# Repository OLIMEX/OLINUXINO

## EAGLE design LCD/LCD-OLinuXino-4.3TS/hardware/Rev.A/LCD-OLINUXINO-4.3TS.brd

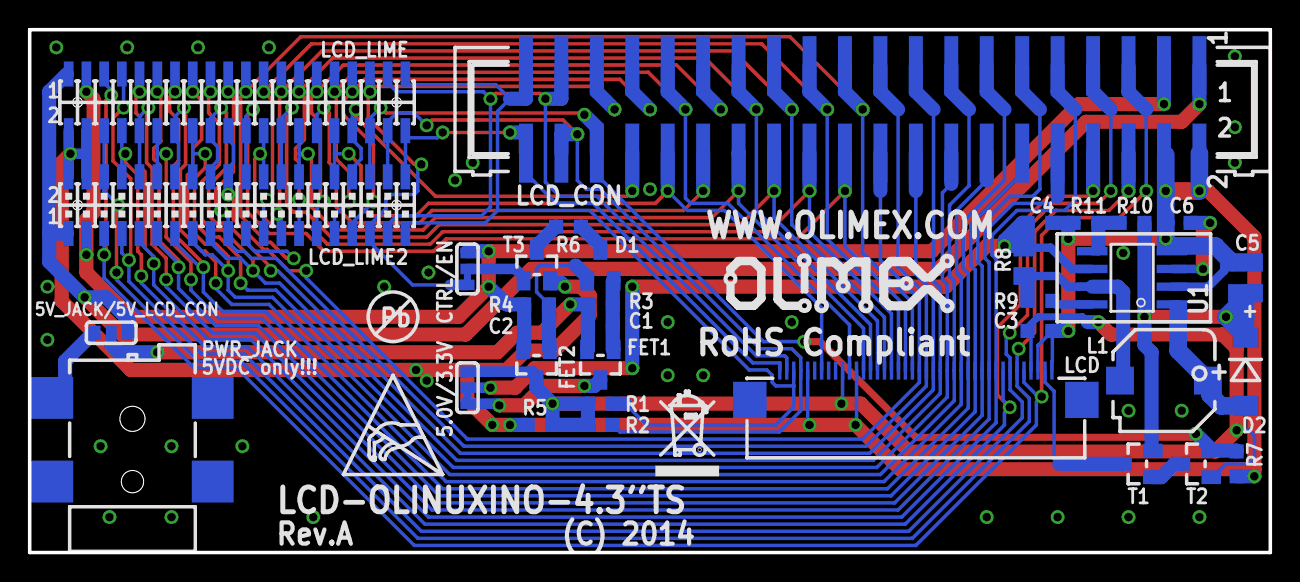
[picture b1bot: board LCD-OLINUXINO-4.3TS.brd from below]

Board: 2 copper layers, 88.9 x 37.5 mm, 38 parts (38 on the bottom side), 57 nets.

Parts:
5.0V/3.3V: 5.0V:Close/3.3V:Open; SJ_2_SMALL_23_TIED
5V_JACK/5V_LCD_CON: 5V_JACK:Open/5V_LCD_CON:Close; SJ_2_SMALL
C1, C3, C4: 22uF/6.3V; C0603_DWS
C2: 100n; C0603_DWS
C5: 100uF/35V/6.3x11; CP6.3X11-H-M
C6: 470pF; C0603_DWS
CTRL/EN: CTRL:Close/EN:Open; SJ_2_SMALL_23_TIED
D1: BAT54C; SOT23C
D2: 1N5819S(SS14); MLL-41
FET1, FET2: IRLML6402; SOT23
L1: 220uH/SD75; CLXXUH_SD73
LCD: BT043DC+(FPV-WZA21-40-LF); FPV-WZA21-40-LF
LCD_CON: ML40-GBH-254-SMT-40; ML40-MALE(GBH-254-SMT-40)
LCD_LIME: GPH127SMT-02X20; YA-V36P-2X20-LF
LCD_LIME2: GPH127SMT-02X20; GPH127SMT-02X20(PA-V16X-2X20-LF)
PWR_JACK: DCJ-W54R-20-LF; PWR-JACK-SMD
R1, R2: NA; R0603_5MIL_DWS
R3, R4, R10: 27k/1%; R0603_5MIL_DWS
R5: 10k; R0603_5MIL_DWS
R6: 1k; R0603_5MIL_DWS
R7, R11: 1.2k/1%; R0603_5MIL_DWS
R8: 1R; R0805_5MIL_DWS
R9: 150R; R0603_5MIL_DWS
T1: DTA114YKA; SOT-23
T2, T3: DTC114YKA; SOT-23
U1: MC34063AD(R2)G,(SO8); SO-8
U$4: PB_SMALL
U$8: OLIMEX1_V
U$10: ESD_SYMBOL
U$11: RECYCLE_BIN1/8

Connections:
3.3VDC: C2.1, CTRL/EN.1, FET2.2, LCD_CON.3, LCD_LIME.3, LCD_LIME2.3, R4.2
5VDC: 5V_JACK/5V_LCD_CON.2, C1.1, FET1.2, R3.2
+5V: 5.0V/3.3V.2, C4.1, R8.1, U1.6
+12V: C5.+, D2.K, R10.2, T1.2
GND: C3.2, C4.2, C5.-, C6.2, LCD.1, LCD.3, LCD.29, LCD.36, LCD_CON.2, LCD_CON.4, LCD_LIME.2, LCD_LIME.4, LCD_LIME2.2, LCD_LIME2.4, PWR_JACK.2, PWR_JACK.3, R5.1, R7.1, R11.1, T3.2, U1.2, U1.4
LCD_B0: LCD.21, LCD_CON.21, LCD_LIME.21, LCD_LIME2.21
LCD_B1: LCD.22, LCD_CON.22, LCD_LIME.22, LCD_LIME2.22
LCD_B2: LCD.23, LCD_CON.23, LCD_LIME.23, LCD_LIME2.23
LCD_B3: LCD.24, LCD_CON.24, LCD_LIME.24, LCD_LIME2.24
LCD_B4: LCD.25, LCD_CON.25, LCD_LIME.25, LCD_LIME2.25
LCD_B5: LCD.26, LCD_CON.26, LCD_LIME.26, LCD_LIME2.26
LCD_B6: LCD.27, LCD_CON.27, LCD_LIME.27, LCD_LIME2.27
LCD_B7: LCD.28, LCD_CON.28, LCD_LIME.28, LCD_LIME2.28
LCD_BKL: LCD_CON.36, LCD_LIME.36, LCD_LIME2.36, R7.2, T2.2
LCD_CLK: LCD.30, LCD_CON.31, LCD_LIME.31, LCD_LIME2.31
LCD_DE: LCD.34, LCD_CON.32, LCD_LIME.32, LCD_LIME2.32
LCD_G0: LCD.13, LCD_CON.13, LCD_LIME.13, LCD_LIME2.13
LCD_G1: LCD.14, LCD_CON.14, LCD_LIME.14, LCD_LIME2.14
LCD_G2: LCD.15, LCD_CON.15, LCD_LIME.15, LCD_LIME2.15
LCD_G3: LCD.16, LCD_CON.16, LCD_LIME.16, LCD_LIME2.16
LCD_G4: LCD.17, LCD_CON.17, LCD_LIME.17, LCD_LIME2.17
LCD_G5: LCD.18, LCD_CON.18, LCD_LIME.18, LCD_LIME2.18
LCD_G6: LCD.19, LCD_CON.19, LCD_LIME.19, LCD_LIME2.19
LCD_G7: LCD.20, LCD_CON.20, LCD_LIME.20, LCD_LIME2.20
LCD_PWRE: CTRL/EN.3, LCD_CON.35, LCD_LIME.35, LCD_LIME2.35
LCD_R0: LCD.5, LCD_CON.5, LCD_LIME.5, LCD_LIME2.5
LCD_R1: LCD.6, LCD_CON.6, LCD_LIME.6, LCD_LIME2.6
LCD_R2: LCD.7, LCD_CON.7, LCD_LIME.7, LCD_LIME2.7
LCD_R3: LCD.8, LCD_CON.8, LCD_LIME.8, LCD_LIME2.8
LCD_R4: LCD.9, LCD_CON.9, LCD_LIME.9, LCD_LIME2.9
LCD_R5: LCD.10, LCD_CON.10, LCD_LIME.10, LCD_LIME2.10
LCD_R6: LCD.11, LCD_CON.11, LCD_LIME.11, LCD_LIME2.11
LCD_R7: LCD.12, LCD_CON.12, LCD_LIME.12, LCD_LIME2.12
unnamed: 5.0V/3.3V.3, FET1.3
unnamed: T1.1, T2.3
unnamed: LCD_CON.29, LCD_LIME.29, LCD_LIME2.29
unnamed: LCD_CON.33, LCD_LIME.33, LCD_LIME2.33
unnamed: LCD_CON.30, LCD_LIME.30, LCD_LIME2.30
unnamed: LCD_CON.34, LCD_LIME.34, LCD_LIME2.34
unnamed: C2.2, D1.1, FET2.1, R4.1
unnamed: C1.2, D1.2, FET1.1, R3.1
unnamed: 5V_JACK/5V_LCD_CON.3, LCD_CON.1, LCD_LIME.1, LCD_LIME2.1
unnamed: R6.1, T3.3
unnamed: CTRL/EN.2, T3.1
unnamed: D1.3, R6.2
unnamed: 5V_JACK/5V_LCD_CON.1, PWR_JACK.1
unnamed: R10.1, R11.2, U1.5
unnamed: C6.1, U1.3
unnamed: D2.A, L1.2, U1.1
unnamed: L1.1, R8.2, R9.2, U1.7
unnamed: R9.1, U1.8
TPX1: LCD.37, LCD_CON.38, LCD_LIME.38, LCD_LIME2.38, R2.2
TPX2: LCD.39, LCD_CON.37, LCD_LIME.37, LCD_LIME2.37
TPY1: LCD.38, LCD_CON.39, LCD_LIME.39, LCD_LIME2.39, R1.2
TPY2: LCD.40, LCD_CON.40, LCD_LIME.40, LCD_LIME2.40
VCC: 5.0V/3.3V.1, C3.1, FET2.3, LCD.4, LCD.31, R1.1, R2.1, R5.2, T2.1
VLED+: LCD.2, T1.3

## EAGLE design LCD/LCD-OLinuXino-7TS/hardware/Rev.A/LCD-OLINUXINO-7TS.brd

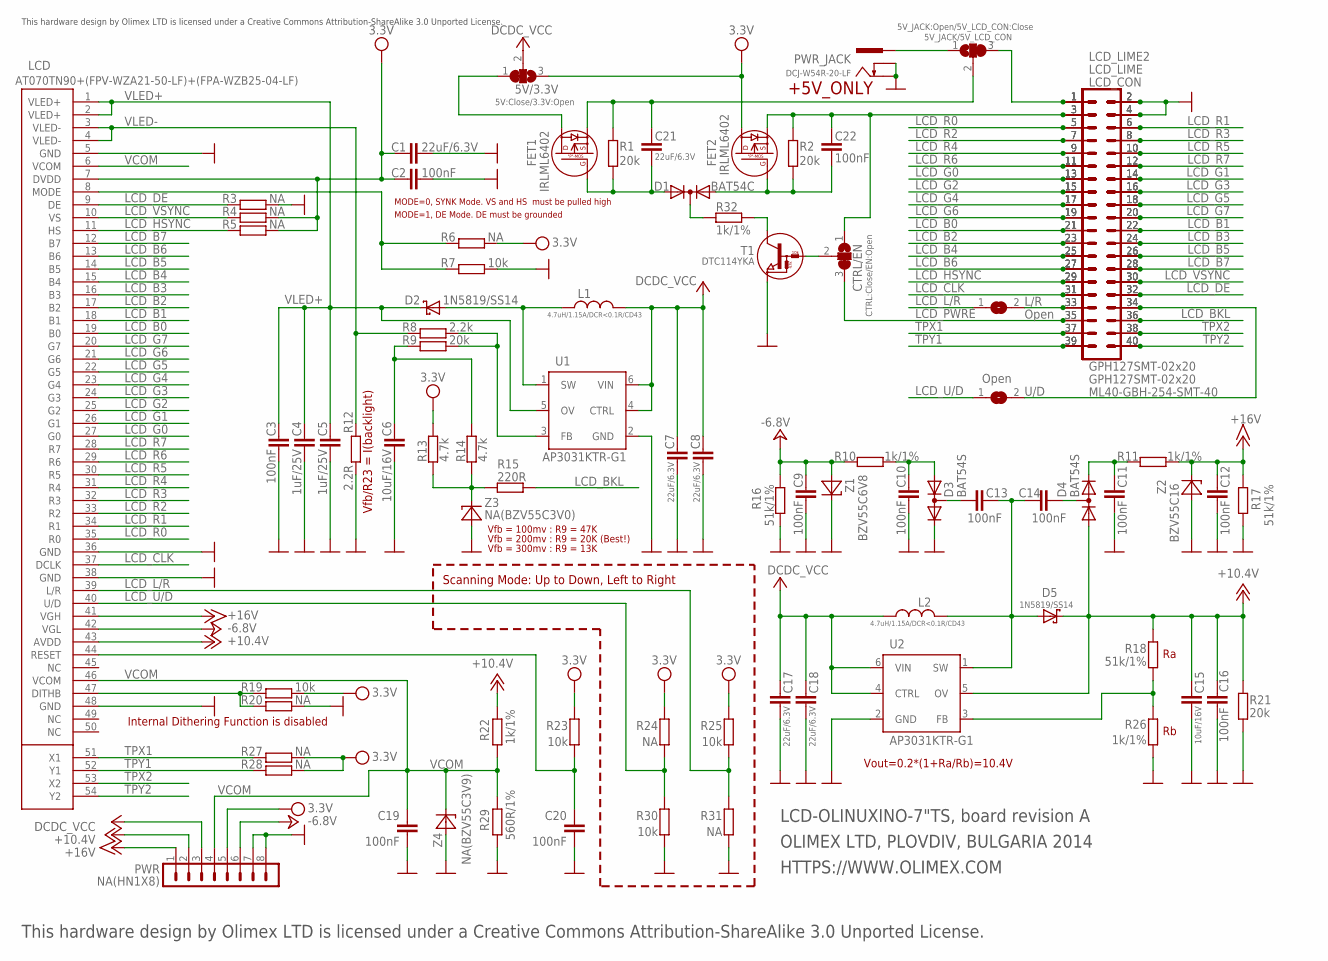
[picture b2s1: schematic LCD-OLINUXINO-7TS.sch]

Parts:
5V/3.3V: 5V:Close/3.3V:Open; SJ_2_SMALL
5V_JACK/5V_LCD_CON: 5V_JACK:Open/5V_LCD_CON:Close; SJ_2_SMALL
C1, C7, C8, C17, C18, C21: 22uF/6.3V; C0603_DWS
C2, C3, C9, C10, C11, C12, C13, C14, C16, C19, C20, C22: 100nF; C0603_DWS
C4, C5: 1uF/25V; C0805_5MIL_DWS
C6, C15: 10uF/16V; C0805_5MIL_DWS
CTRL/EN: CTRL:Close/EN:Open; SJ_2_SMALL_23_TIED
D1: BAT54C; SOT23C
D2, D5: 1N5819/SS14; MLL-41
D3, D4: BAT54S; SOT23C(BAT54S)
FET1, FET2: IRLML6402; SOT23
L1, L2: 4.7uH/1.15A/DCR<0.1R/CD43; CD42(43)
L/R: Open; SJ_1_SMALLER
LCD: AT070TN90+(FPV-WZA21-50-LF)+(FPA-WZB25-04-LF); LCD7"_TOUCH(AT070TN90)
LCD_CON: ML40-GBH-254-SMT-40; ML40-MALE(GBH-254-SMT-40)
LCD_LIME: GPH127SMT-02x20; YA-V36P-2X20-LF
LCD_LIME2: GPH127SMT-02x20; GPH127SMT-02X20(PA-V16X-2X20-LF)
PWR: NA(HN1X8); HN1X8
PWR_JACK: DCJ-W54R-20-LF; PWR-JACK-SMD
R1, R2, R9, R21: 20k; R0603_5MIL_DWS
R3, R4, R5, R6, R20, R24, R27, R28, R31: NA; R0603_5MIL_DWS
R7, R19, R23, R25, R30: 10k; R0603_5MIL_DWS
R8: 2.2k; R0603_5MIL_DWS
R10, R11, R22, R26, R32: 1k/1%; R0603_5MIL_DWS
R12: 2.2R; R0603_5MIL_DWS
R13, R14: 4.7k; R0603_5MIL_DWS
R15: 220R; R0603_5MIL_DWS
R16, R17, R18: 51k/1%; R0603_5MIL_DWS
R29: 560R/1%; R0603_5MIL_DWS
T1: DTC114YKA; SOT-23
U1, U2: AP3031KTR-G1; SOT23-6
U/D: Open; SJ_1_SMALLER
Z1: BZV55C6V8; MINI-MELF
Z2: BZV55C16; MINI-MELF
Z3: NA(BZV55C3V0); MINI-MELF
Z4: NA(BZV55C3V9); MINI-MELF

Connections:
+5V: 5V/3.3V.2, C7.2, C8.2, C17.2, C18.2, L1.1, L2.1, PWR.3, U1.4 (CTRL), U1.6 (VIN), U2.4 (CTRL), U2.6 (VIN)
+12V: C15.1, C16.1, D4.1 (A), D5.K (C), LCD.43 (AVDD), PWR.2, R18.2, R21.2, R22.1, U2.5 (OV)
+15V: C12.1, LCD.41 (VGH), PWR.1, R11.1, R17.2, Z2.1 (C)
-24V: C9.1, LCD.42 (VGL), PWR.6, R10.1, R16.2, Z1.2 (A)
GND: C1.2, C2.2, C3.2, C4.2, C5.2, C6.2, C7.1, C8.1, C9.2, C10.2, C11.2, C12.2, C15.2, C16.2, C17.1, C18.1, C19.2, C20.2, D3.2 (K), LCD.5 (GND), LCD.36 (GND), LCD.38 (GND), LCD.48 (GND), LCD_CON.2, LCD_CON.4, LCD_LIME.2, LCD_LIME.4, LCD_LIME2.2, LCD_LIME2.4, PWR.7, PWR.8, PWR_JACK.2 (-), PWR_JACK.3 (--), R3.1, R7.1, R12.2, R16.1, R17.1, R20.1, R21.1, R26.2, R29.2, R30.2, R31.2, T1.2 (E), U1.2 (GND), U2.2 (GND), Z1.1 (C), Z2.2 (A), Z3.2 (A), Z4.2 (A)
LCD_B0: LCD.19 (B0), LCD_CON.21, LCD_LIME.21, LCD_LIME2.21
LCD_B1: LCD.18 (B1), LCD_CON.22, LCD_LIME.22, LCD_LIME2.22
LCD_B2: LCD.17 (B2), LCD_CON.23, LCD_LIME.23, LCD_LIME2.23
LCD_B3: LCD.16 (B3), LCD_CON.24, LCD_LIME.24, LCD_LIME2.24
LCD_B4: LCD.15 (B4), LCD_CON.25, LCD_LIME.25, LCD_LIME2.25
LCD_B5: LCD.14 (B5), LCD_CON.26, LCD_LIME.26, LCD_LIME2.26
LCD_B6: LCD.13 (B6), LCD_CON.27, LCD_LIME.27, LCD_LIME2.27
LCD_B7: LCD.12 (B7), LCD_CON.28, LCD_LIME.28, LCD_LIME2.28
LCD_BKL: LCD_CON.36, LCD_LIME.36, LCD_LIME2.36, R15.1
LCD_CLK: LCD.37 (DCLK), LCD_CON.31, LCD_LIME.31, LCD_LIME2.31
LCD_DE: LCD.9 (DE), LCD_CON.32, LCD_LIME.32, LCD_LIME2.32, R3.2
LCD_G0: LCD.27 (G0), LCD_CON.13, LCD_LIME.13, LCD_LIME2.13
LCD_G1: LCD.26 (G1), LCD_CON.14, LCD_LIME.14, LCD_LIME2.14
LCD_G2: LCD.25 (G2), LCD_CON.15, LCD_LIME.15, LCD_LIME2.15
LCD_G3: LCD.24 (G3), LCD_CON.16, LCD_LIME.16, LCD_LIME2.16
LCD_G4: LCD.23 (G4), LCD_CON.17, LCD_LIME.17, LCD_LIME2.17
LCD_G5: LCD.22 (G5), LCD_CON.18, LCD_LIME.18, LCD_LIME2.18
LCD_G6: LCD.21 (G6), LCD_CON.19, LCD_LIME.19, LCD_LIME2.19
LCD_G7: LCD.20 (G7), LCD_CON.20, LCD_LIME.20, LCD_LIME2.20
LCD_HSYNC: LCD.11 (HS), LCD_CON.29, LCD_LIME.29, LCD_LIME2.29, R5.2
LCD_L/R: L/R.1, LCD.39 (L/R), R25.2, R31.1
LCD_PWRE: CTRL/EN.3, LCD_CON.35, LCD_LIME.35, LCD_LIME2.35
LCD_R0: LCD.35 (R0), LCD_CON.5, LCD_LIME.5, LCD_LIME2.5
LCD_R1: LCD.34 (R1), LCD_CON.6, LCD_LIME.6, LCD_LIME2.6
LCD_R2: LCD.33 (R2), LCD_CON.7, LCD_LIME.7, LCD_LIME2.7
LCD_R3: LCD.32 (R3), LCD_CON.8, LCD_LIME.8, LCD_LIME2.8
LCD_R4: LCD.31 (R4), LCD_CON.9, LCD_LIME.9, LCD_LIME2.9
LCD_R5: LCD.30 (R5), LCD_CON.10, LCD_LIME.10, LCD_LIME2.10
LCD_R6: LCD.29 (R6), LCD_CON.11, LCD_LIME.11, LCD_LIME2.11
LCD_R7: LCD.28 (R7), LCD_CON.12, LCD_LIME.12, LCD_LIME2.12
LCD_U/D: LCD.40 (U/D), R24.2, R30.1, U/D.1
LCD_VSYNC: LCD.10 (VS), LCD_CON.30, LCD_LIME.30, LCD_LIME2.30, R4.2
unnamed: LCD.8 (MODE), R6.2, R7.2
unnamed: C14.2, D4.3 (AK)
unnamed: C22.1, CTRL/EN.1, FET2.2 (S), LCD_CON.3, LCD_LIME.3, LCD_LIME2.3, R2.2
unnamed: C11.1, D4.2 (K), R11.2
unnamed: R8.1, R9.1, U1.3 (FB)
unnamed: C10.1, D3.1 (A), R10.2
unnamed: 5V_JACK/5V_LCD_CON.2, C21.1, FET1.2 (S), R1.2
unnamed: C22.2, D1.1 (A1), FET2.1 (G), R2.1
unnamed: C21.2, D1.2 (A2), FET1.1 (G), R1.1
unnamed: C13.1, D3.3 (AK)
unnamed: R32.1, T1.3 (C)
unnamed: C6.1, R9.2, R14.2
unnamed: D2.A, L1.2, U1.1 (SW)
unnamed: R13.1, R14.1, R15.2, Z3.1 (C)
unnamed: L/R.2, LCD_CON.33, LCD_LIME.33, LCD_LIME2.33
unnamed: CTRL/EN.2, T1.1 (B)
unnamed: LCD_CON.34, LCD_LIME.34, LCD_LIME2.34, U/D.2
unnamed: 5V/3.3V.1, FET1.3 (D)
unnamed: D1.3 (K), R32.2
unnamed: 5V_JACK/5V_LCD_CON.1, PWR_JACK.1 (+)
unnamed: 5V_JACK/5V_LCD_CON.3, LCD_CON.1, LCD_LIME.1, LCD_LIME2.1
unnamed: LCD.47 (DITHB), R19.2, R20.2
unnamed: C13.2, C14.1, D5.A, L2.2, U2.1 (SW)
unnamed: R18.1, R26.1, U2.3 (FB)
RESET: C20.1, LCD.44 (RESET), R23.2
TPX1: LCD.51 (X1), LCD_CON.37, LCD_LIME.37, LCD_LIME2.37, R27.2
TPX2: LCD.53 (X2), LCD_CON.38, LCD_LIME.38, LCD_LIME2.38
TPY1: LCD.52 (Y1), LCD_CON.39, LCD_LIME.39, LCD_LIME2.39, R28.2
TPY2: LCD.54 (Y2), LCD_CON.40, LCD_LIME.40, LCD_LIME2.40
VCC: 5V/3.3V.3, C1.1, C2.1, FET2.3 (D), LCD.7 (DVDD), PWR.5, R4.1, R5.1, R6.1, R13.2, R19.1, R23.1, R24.1, R25.1, R27.1, R28.1
VCOM: C19.1, LCD.6 (VCOM), LCD.46 (VCOM), PWR.4, R22.2, R29.1, Z4.1 (C)
VLED+: C3.1, C4.1, C5.1, D2.K (C), LCD.1 (VLED+), LCD.2 (VLED+), U1.5 (OV)
VLED-: LCD.3 (VLED-), LCD.4 (VLED-), R8.2, R12.1

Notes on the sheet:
Vfb/R23 = I(backlight)
Vfb = 200mv : R9 = 20K (Best!)
Vfb = 100mv : R9 = 47K
Vfb = 300mv : R9 = 13K
MODE=0, SYNK Mode. VS and HS must be pulled high
MODE=1, DE Mode. DE must be grounded
Scanning Mode: Up to Down, Left to Right
Vout=0.2*(1+Ra/Rb)=10.4V
Internal Dithering Function is disabled
+5V_ONLY
5V_JACK:Open/5V_LCD_CON:Close
LCD-OLINUXINO-7"TS, board revision A
OLIMEX LTD, PLOVDIV, BULGARIA 2014
HTTPS://WWW.OLIMEX.COM
This hardware design by Olimex LTD is licensed under a Creative Commons Attribution-ShareAlike 3.0 Unported License.

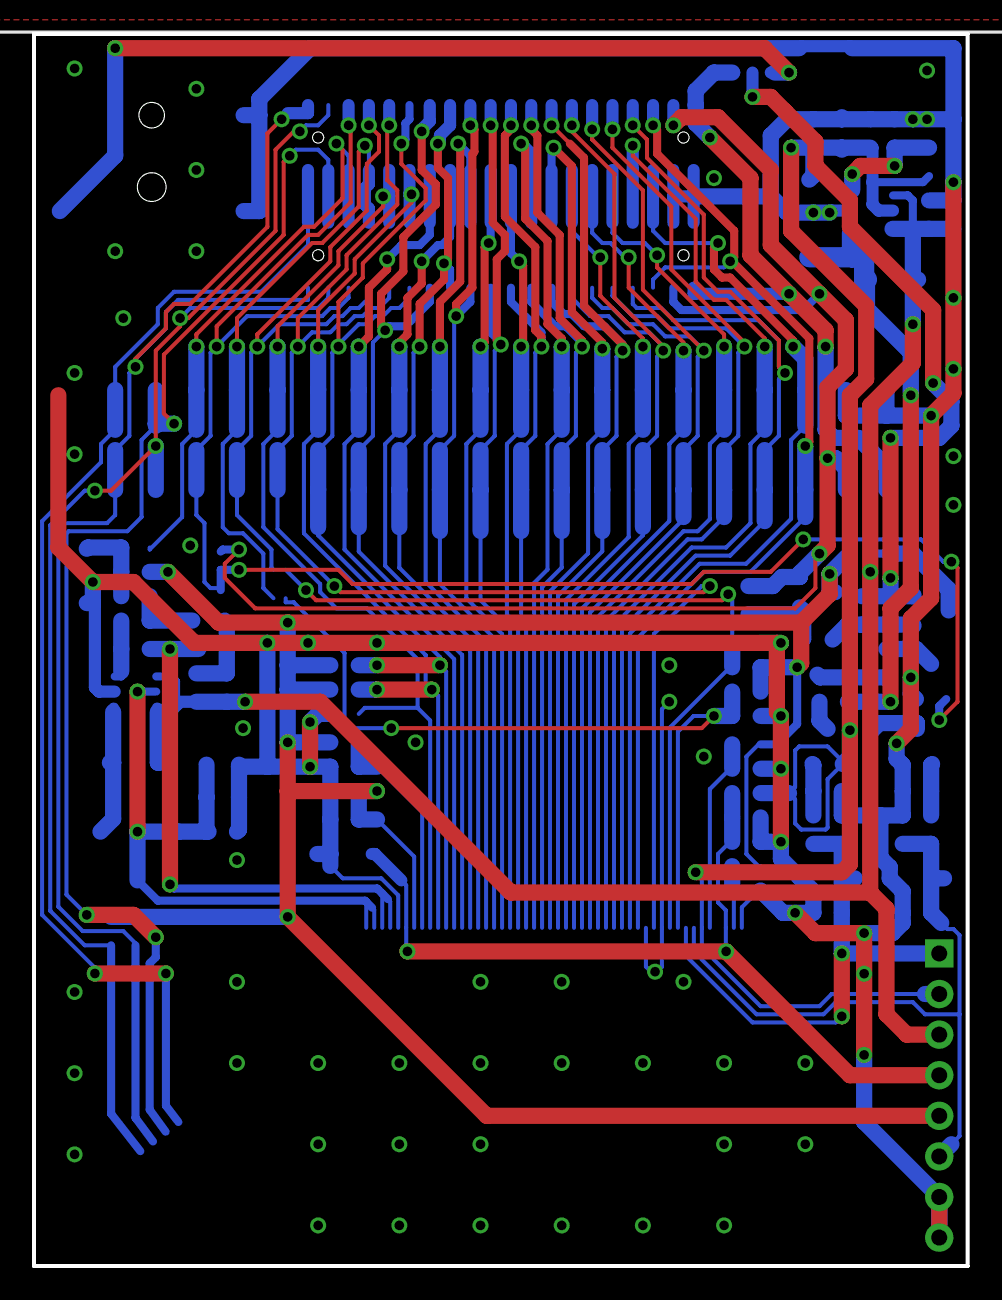
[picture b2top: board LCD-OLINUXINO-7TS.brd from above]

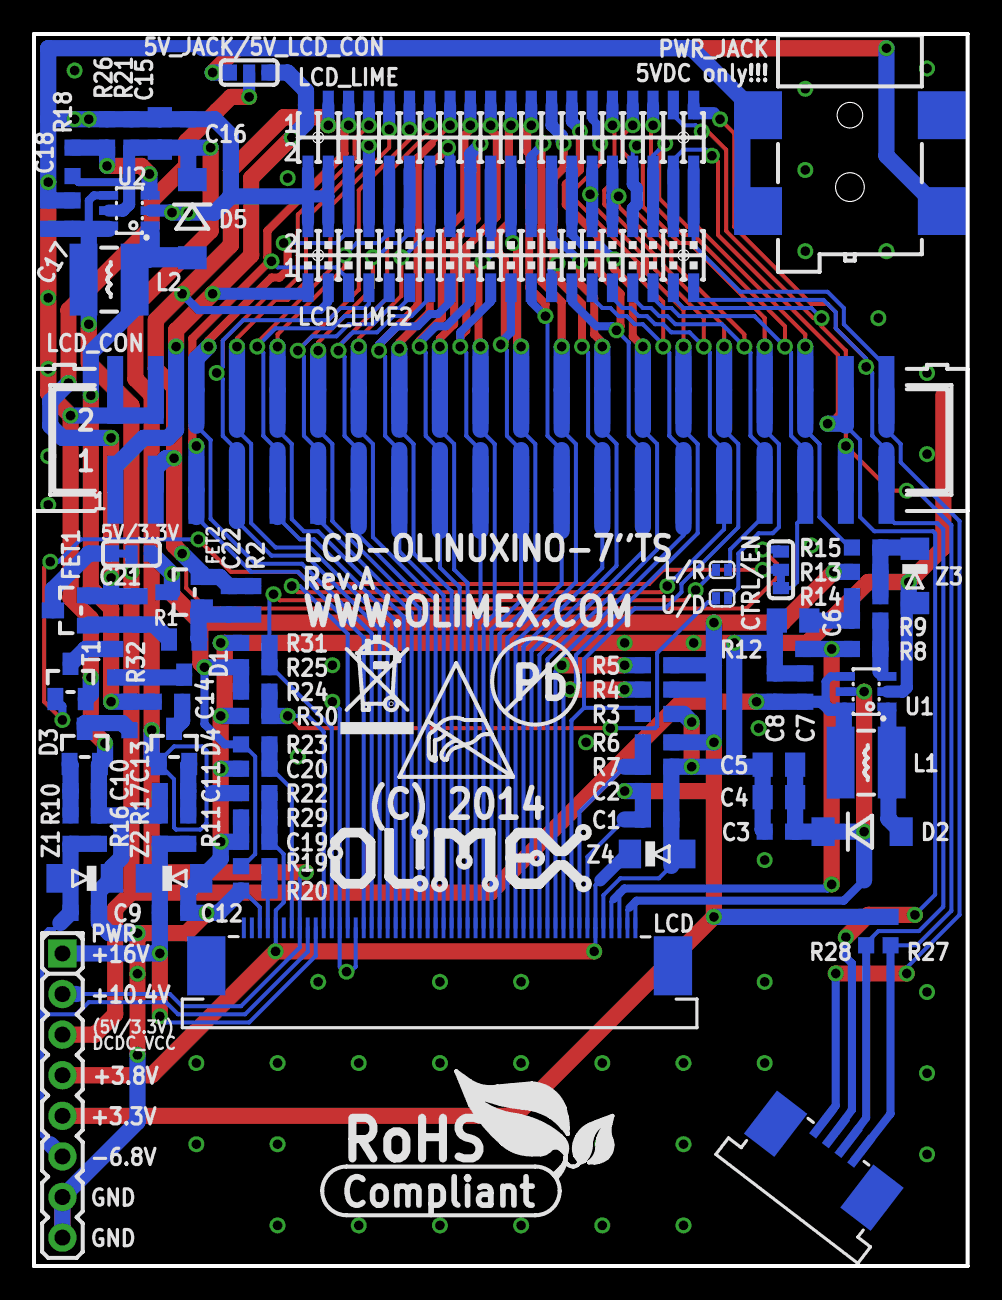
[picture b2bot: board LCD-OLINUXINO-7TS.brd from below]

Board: 2 copper layers, 58.4 x 77.1 mm, 86 parts (85 on the bottom side), 70 nets.

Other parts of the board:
U$8: OLIMEX1_V
U$9: PB
U$10: ESD_SYMBOL
U$11: RECYCLE_BIN1/8
U$12: ROHS

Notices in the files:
LCD/LCD-OLinuXino-4.3TS/hardware/Rev.A/LCD-OLINUXINO-4.3TS.brd:
(C) 2014
